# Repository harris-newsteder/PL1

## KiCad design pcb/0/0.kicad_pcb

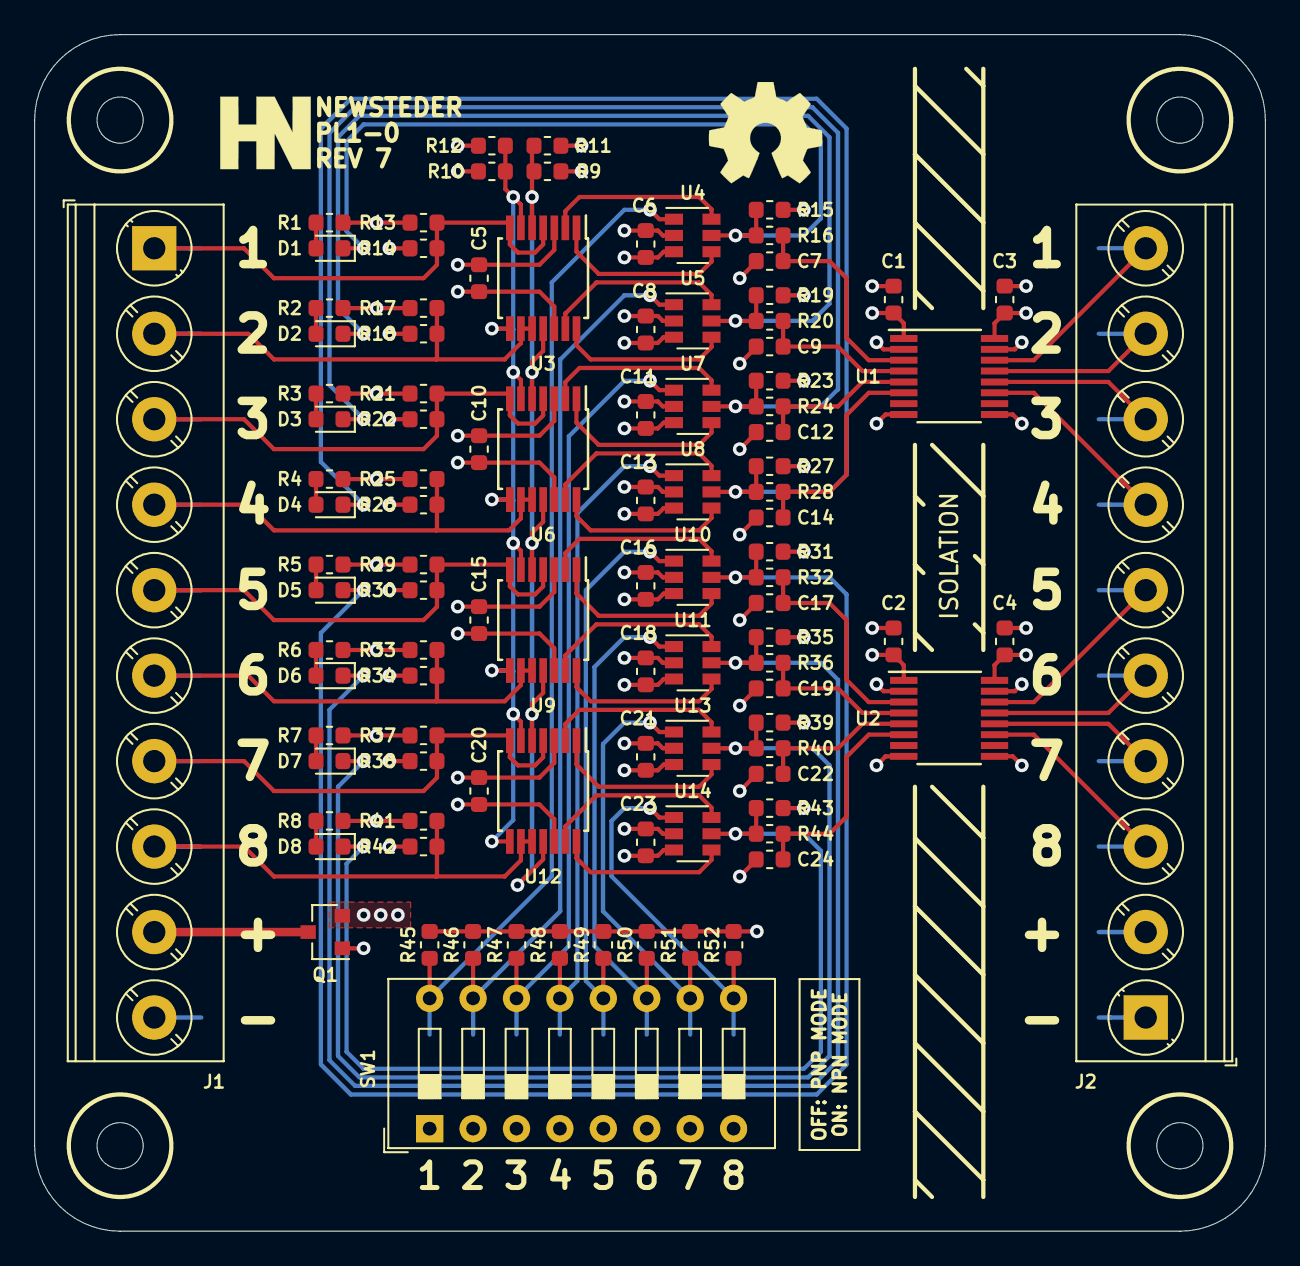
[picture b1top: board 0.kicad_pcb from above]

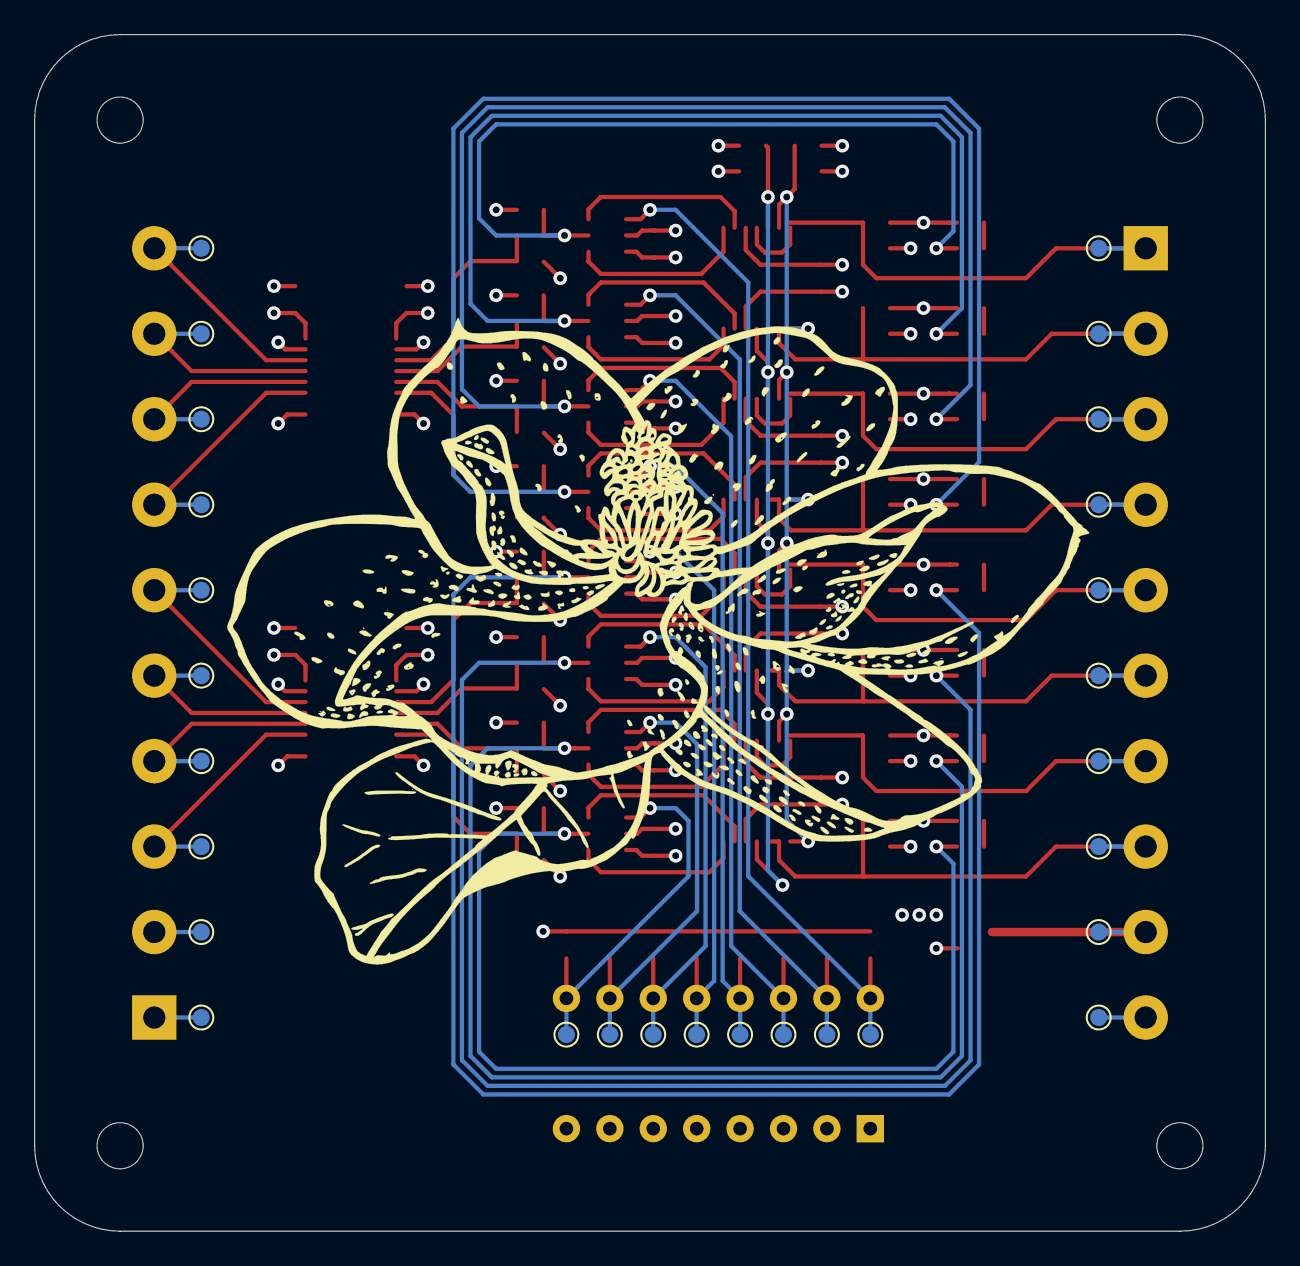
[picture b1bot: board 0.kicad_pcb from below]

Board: 4 copper layers, 72.0 x 70.0 mm, 130 parts (28 on the bottom side), 71 nets.

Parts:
C1, C2, C3, C4, C5, C6, C7, C8, C9, C10, C11, C12, C13, C14, C15, C16, C17, C18, C19, C20, C21, C22, C23, C24: 0.1uF; C_0603_1608Metric
D1, D2, D3, D4, D5, D6, D7, D8: LED; LED_0603_1608Metric
J1: INPUT TERMINAL; TerminalBlock_Phoenix_PT-1,5-10-5.0-H_1x10_P5.00mm_Horizont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
J2: OUTPUT TERMINAL; TerminalBlock_Phoenix_PT-1,5-10-5.0-H_1x10_P5.00mm_Horizont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
Q1: ZXMP10A13FTA; SOT-23
R1, R2, R3, R4, R5, R6, R7, R8: 1k; R_0603_1608Metric
R9: 240R; R_0603_1608Metric
R10: 732R; R_0603_1608Metric
R11: 360R; R_0603_1608Metric
R12: 316R; R_0603_1608Metric
R13, R14, R15, R16, R17, R18, R19, R20, R21, R22, R23, R24, R25, R26, R27, R28, R29, R30, R31, R32, R33, R34, R35, R36, R37, R38, R39, R40, R41, R42, R43, R44, R45, R46, R47, R48, R49, R50, R51, R52: 10k; R_0603_1608Metric
SW1: MODE SELECT SWITCH; SW_DIP_SPSTx08_Slide_9.78x22.5mm_W7.62mm_P2.54mm
TP1, TP2, TP3, TP4, TP5, TP6, TP7, TP8, TP9, TP10, TP11, TP12, TP13, TP14, TP15, TP16, TP17, TP18, TP19, TP20, TP21, TP22, TP23, TP24, TP25, TP26, TP27, TP28: TestPoint; TestPoint_Pad_D1.0mm
U1, U2: Si8645BA-B-IU; QSOP-16_3.9x4.9mm_P0.635mm
U3, U6, U9, U12: LM339; TSSOP-14_4.4x5mm_P0.65mm
U4, U5, U7, U8, U10, U11, U13, U14: STG719STR; SOT-23-6

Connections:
1.5V: R10.2, R12.1, U3.6, U3.8, U6.6, U6.8, U9.6, U9.8, U12.6, U12.8
3.0V: R9.2, R11.1, U3.5, U3.11, U6.5, U6.11, U9.5, U9.11, U12.5, U12.11
+5V: C1.2, C2.2, C5.1, C6.1, C8.1, C10.1, C11.1, C13.1, C15.1, C16.1, C18.1, C20.1, C21.1, C23.1, Q1.2, R1.1, R2.1, R3.1, R4.1, R5.1, R6.1, R7.1, R8.1, R9.1, R10.1, R13.1, R15.1, R17.1, R19.1, R21.1, R23.1, R25.1, R27.1, R29.1, R31.1, R33.1, R35.1, R37.1, R39.1, R41.1, R43.1, R45.1, R46.1, R47.1, R48.1, R49.1, R50.1, R51.1, R52.1, U1.1, U2.1, U3.3, U4.2, U5.2, U6.3, U7.2, U8.2, U9.3, U10.2, U11.2, U12.3, U13.2, U14.2
/IN_1: J1.1, R13.2, R14.1, TP1.1, U3.4, U3.7
/IN_2: J1.2, R17.2, R18.1, TP2.1, U3.9, U3.10
/IN_3: J1.3, R21.2, R22.1, TP3.1, U6.4, U6.7
/IN_4: J1.4, R25.2, R26.1, TP4.1, U6.9, U6.10
/IN_5: J1.5, R29.2, R30.1, TP5.1, U9.4, U9.7
/IN_6: J1.6, R33.2, R34.1, TP6.1, U9.9, U9.10
/IN_7: J1.7, R37.2, R38.1, TP7.1, U12.4, U12.7
/IN_8: J1.8, R41.2, R42.1, TP8.1, U12.9, U12.10
/MODE_1: R45.2, SW1.16, TP9.1, U4.1
/MODE_2: R46.2, SW1.15, TP10.1, U5.1
/MODE_3: R47.2, SW1.14, TP11.1, U7.1
/MODE_4: R48.2, SW1.13, TP12.1, U8.1
/MODE_5: R49.2, SW1.12, TP13.1, U10.1
/MODE_6: R50.2, SW1.11, TP14.1, U11.1
/MODE_7: R51.2, SW1.10, TP15.1, U13.1
/MODE_8: R52.2, SW1.9, TP16.1, U14.1
/OUT_1: J2.10, TP17.1, U1.14
/OUT_2: J2.9, TP18.1, U1.13
/OUT_3: J2.8, TP19.1, U1.12
/OUT_4: J2.7, TP20.1, U1.11
/OUT_5: J2.6, TP21.1, U2.14
/OUT_6: J2.5, TP22.1, U2.13
/OUT_7: J2.4, TP23.1, U2.12
/OUT_8: J2.3, TP24.1, U2.11
/UOUT_1: C7.1, R16.1, U1.3
/UOUT_2: C9.1, R20.1, U1.4
/UOUT_3: C12.1, R24.1, U1.5
/UOUT_4: C14.1, R28.1, U1.6
/UOUT_5: C17.1, R32.1, U2.3
/UOUT_6: C19.1, R36.1, U2.4
/UOUT_7: C22.1, R40.1, U2.5
/UOUT_8: C24.1, R44.1, U2.6
GND: C1.1, C2.1, C5.2, C6.2, C7.2, C8.2, C9.2, C10.2, C11.2, C12.2, C13.2, C14.2, C15.2, C16.2, C17.2, C18.2, C19.2, C20.2, C21.2, C22.2, C23.2, C24.2, J1.10, Q1.1, R11.2, R12.2, R14.2, R18.2, R22.2, R26.2, R30.2, R34.2, R38.2, R42.2, SW1.1, SW1.2, SW1.3, SW1.4, SW1.5, SW1.6, SW1.7, SW1.8, TP25.1, U1.2, U1.8, U2.2, U2.8, U3.12, U4.3, U5.3, U6.12, U7.3, U8.3, U9.12, U10.3, U11.3, U12.12, U13.3, U14.3
LV+: C3.2, C4.2, J2.2, TP28.1, U1.16, U2.16
LV-: C3.1, C4.1, J2.1, TP27.1, U1.9, U1.15, U2.9, U2.15
unnamed: D1.1, R15.2, R16.2, U4.5
unnamed: D1.2, R1.2
unnamed: D2.1, R19.2, R20.2, U5.5
unnamed: D2.2, R2.2
unnamed: D3.1, R23.2, R24.2, U7.5
unnamed: D3.2, R3.2
unnamed: D4.1, R27.2, R28.2, U8.5
unnamed: D4.2, R4.2
unnamed: D5.1, R31.2, R32.2, U10.5
unnamed: D5.2, R5.2
unnamed: D6.1, R35.2, R36.2, U11.5
unnamed: D6.2, R6.2
unnamed: D7.1, R39.2, R40.2, U13.5
unnamed: D7.2, R7.2
unnamed: D8.1, R43.2, R44.2, U14.5
unnamed: D8.2, R8.2
unnamed: J1.9, Q1.3, TP26.1
unnamed: U3.1, U4.4
unnamed: U3.2, U4.6
unnamed: U3.13, U5.6
unnamed: U3.14, U5.4
unnamed: U6.1, U7.4
unnamed: U6.2, U7.6
unnamed: U6.13, U8.6
unnamed: U6.14, U8.4
unnamed: U9.1, U10.4
unnamed: U9.2, U10.6
unnamed: U9.14, U11.4
unnamed: U9.13, U11.6
unnamed: U12.1, U13.4
unnamed: U12.2, U13.6
unnamed: U12.13, U14.6
unnamed: U12.14, U14.4

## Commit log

2020-06-17 rev 7 commit, crowd supply release version
2020-12-25 starting to transfer the user manual from microsoft word to asciidoc
